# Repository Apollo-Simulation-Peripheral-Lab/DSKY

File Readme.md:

# DSKY Replica
> This project is still a work-in-progress 

This projects aims to create an affordable and easy to manufacture, yet as realistic as possible replica of the DSKY used in the Apollo program to interface with the Apollo Guidance Computer (AGC).

## Quick start

**Do you want a DSKY but can't build one? Buy one [here](https://shop.ortizma.com)**

**Need Help? Join our Discord [here](https://discord.gg/CHZaYj5UNu)**

**Do you just want to have a DSKY display in your web browser?**
  - Make sure you have NodeJS > 18
  - Run start.bat and answer the prompts

**Do you want to build the whole DSKY replica?**
  - Print the .3mf/.stl meshes found in the '3D Models' folder.
    - The recommended display is the **960x544 AMOLED MIPI display**, connected to the Orange Pi via HDMI through an adapter board.
    - A legacy 40-Pin 5" 800x480 LCD variant also exists but is no longer recommended; new builds should use the AMOLED.
  - Order the PCB:
    - The board is designed to be ordered fully assembled from JLCPCB. The fabrication files (gerbers, BOM, pick-and-place positions) are in the ``Boards/Single_board/production`` folder.
  - Calibrate and flash the firmware:
    - Install PlatformIO into VSCode
    - Open this repository's root folder in VSCode — PlatformIO will pick up ``platformio.ini`` at the root
    - Each ATmega328P has a slightly different internal oscillator. You must first determine your chip's optimal OSCCAL value:
      1. Flash the ``bare_calibration`` environment to run the OSCCAL sweep
      2. Use ``firmware/tools/osccal_reader.py`` to read the sweep results and find the best value
      3. Set the ``-DOSC_CAL=0xNN`` flag in ``platformio.ini`` with your value
      4. Flash the ``bare`` environment with your calibrated firmware
  - Set up the Orange Pi:
    - See the [Orange Pi setup guide](Documentation/orangepi-setup.md).
    - Pre-built .img files have been shared around the community, but they are not recommended as they may be out of date.
  - Make sure you have NodeJS > 18
  - Run start.bat on your PC to launch the web display

**Already have a DSKY and want the latest software?**
  - Updates are installed from the DSKY itself: open the menu (press NOUN three times) and go to **SETTINGS → UPDATE**. See [Documentation/updates.md](Documentation/updates.md).

## Repository contents:
* **Documentation**: Useful information to better understand how the different pieces of the puzzle talk to each other. Includes the [Orange Pi setup guide](Documentation/orangepi-setup.md), the [OTA update system](Documentation/updates.md), how to [deploy code to a device over the network](Documentation/deploying-to-a-device.md), and how to [develop on a physical DSKY with hot reload](Documentation/dev-mode.md).
* **2D Models**: SVG files for alarm labels and backlights.
* **3D Models**:
  * **0.4 Nozzle:** All printable meshes (enclosure, display housing, keyboard plate, mounts, etc.) designed for a standard 0.4mm nozzle.
  * **Keys (0.2 Nozzle + AMS).3mf:** Multi-color key models for a 0.2mm nozzle with AMS.
* **Firmware:** PlatformIO project containing the firmware for the bare ATmega328P on the PCB. Includes OSCCAL calibration tooling.
* **Programs:**
  * **next-dsky**: Full-stack Next.js application that serves as the main DSKY UI and backend. Handles serial communication with the PCB, WebSocket connections to AGC simulators, display rendering, and configuration.    * Requirements: NodeJS >18
    * Running: ``npm install`` then ``npm start`` (or use ``start.bat`` from the repo root)
  * **DSKY-Bridge**: Submodule ([nhadrian/DSKY-Bridge](https://github.com/nhadrian/DSKY-Bridge)) — bridge utility for the DSKY.
  * **nassp-cloud**: Node.js service that monitors NASSP (orbiter simulator) telemetry via WebSocket and manages automatic restarts.
  * **click-generator**: Python program that procedurally generates relay clicking audio sequences to emulate the DSKY's relay boxes.
* **Boards**
  * **Single_board**: Unified KiCad PCB project containing the keyboard matrix, alarm lights, serial interface, and backlight driver. The ``production`` folder contains ready-to-order JLCPCB fabrication files.

## License

This project is licensed under [Creative Commons Attribution-NonCommercial-ShareAlike 4.0 International (CC BY-NC-SA 4.0)](LICENSE).

You are free to build one for yourself, modify the design, and share your changes — as long as you **credit the original**, **do not use it commercially**, and **release your derivatives under the same license**. Commercial sale of this device or its derivatives is not permitted without prior written consent from the copyright holder.

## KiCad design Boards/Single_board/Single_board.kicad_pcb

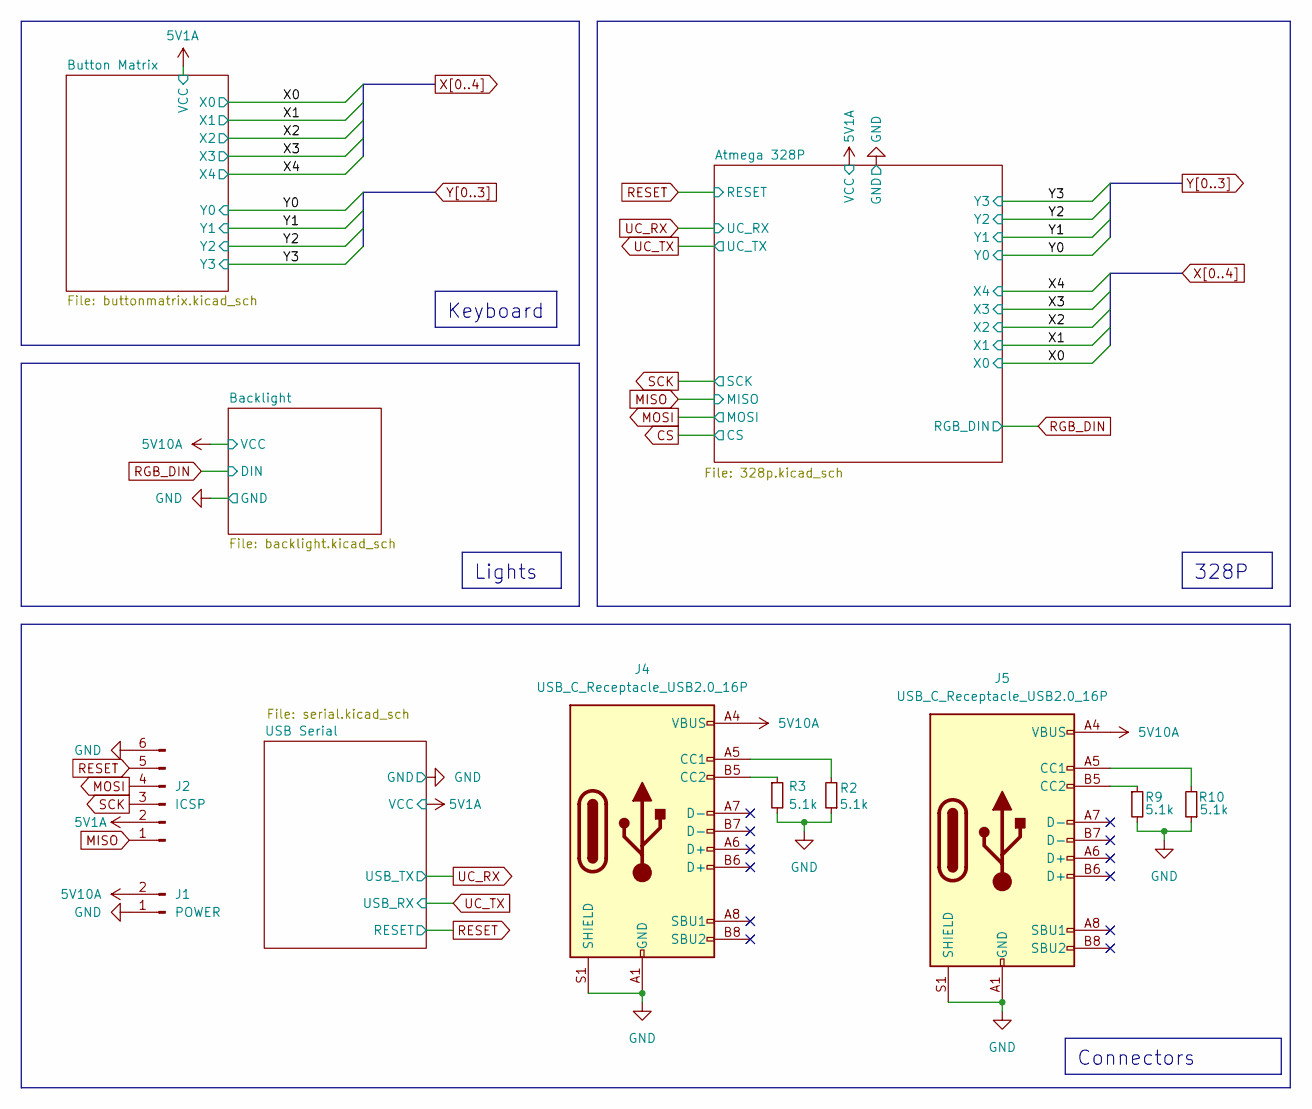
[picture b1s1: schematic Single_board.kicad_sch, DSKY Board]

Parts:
J1: POWER; TerminalBlock_bornier-2_P5.08mm
J2: ICSP; PinHeader_2x03_P2.54mm_Vertical_SMD
J4, J5: USB_C_Receptacle_USB2.0_16P; USB-C-TH_918-468K2029E50001
R2, R3, R9, R10: 5.1k; R_0603_1608Metric

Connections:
5V1A: J2.2; also elsewhere on the board
5V10A: J1.2, J4.A4 (VBUS), J4.A9 (VBUS), J4.B4 (VBUS), J4.B9 (VBUS), J5.A4 (VBUS), J5.A9 (VBUS), J5.B4 (VBUS), J5.B9 (VBUS); also elsewhere on the board
GND: J1.1, J2.6, J4.A1 (GND), J4.A12 (GND), J4.B1 (GND), J4.B12 (GND), J4.S1 (SHIELD), J5.A1 (GND), J5.A12 (GND), J5.B1 (GND), J5.B12 (GND), J5.S1 (SHIELD), R2.1, R3.2, R9.2, R10.1; also elsewhere on the board
MISO: J2.1; also elsewhere on the board
MOSI: J2.4; also elsewhere on the board
unnamed: J4.A5 (CC1), R2.2
unnamed: J4.B5 (CC2), R3.1
unnamed: J5.A5 (CC1), R10.2
unnamed: J5.B5 (CC2), R9.1
RESET: J2.5; also elsewhere on the board
SCK: J2.3; also elsewhere on the board

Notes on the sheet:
Keyboard
328P
Lights
Connectors

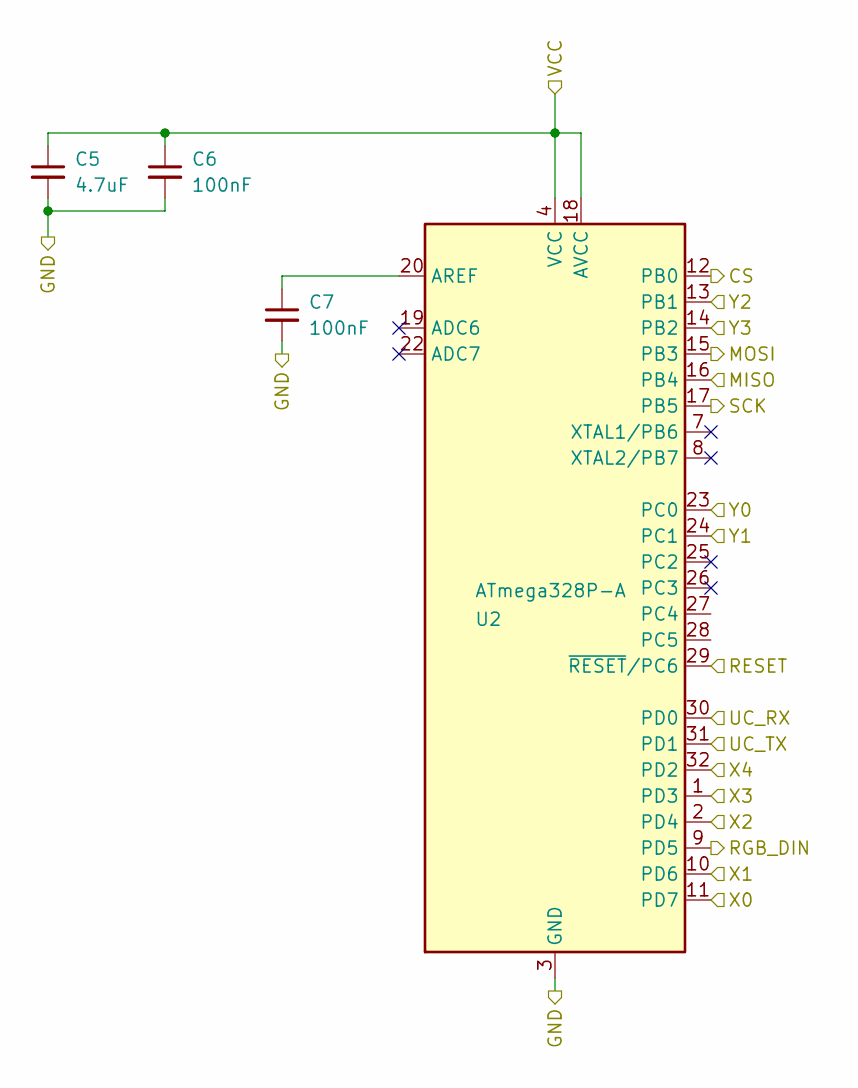
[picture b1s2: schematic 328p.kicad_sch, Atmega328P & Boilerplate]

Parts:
C5: 4.7uF; 0805 4.7uF
C6, C7: 100nF; 0805 100nF
U2: ATmega328P-A; TQFP-32_7x7mm_P0.8mm

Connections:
5V1A: C5.1, C6.1, U2.4 (VCC), U2.6 (VCC), U2.18 (AVCC); also elsewhere on the board
CS: U2.12 (PB0)
GND: C5.2, C6.2, C7.2, U2.3 (GND), U2.5 (GND), U2.21 (GND); also elsewhere on the board
MISO: U2.16 (PB4); also elsewhere on the board
MOSI: U2.15 (PB3); also elsewhere on the board
unnamed: C7.1, U2.20 (AREF)
RESET: U2.29 (~RESET/PC6); also elsewhere on the board
RGB_DIN: U2.9 (PD5); also elsewhere on the board
SCK: U2.17 (PB5); also elsewhere on the board
UC_RX: U2.30 (PD0); also elsewhere on the board
UC_TX: U2.31 (PD1); also elsewhere on the board
X0: U2.11 (PD7); also elsewhere on the board
X1: U2.10 (PD6); also elsewhere on the board
X2: U2.2 (PD4); also elsewhere on the board
X3: U2.1 (PD3); also elsewhere on the board
X4: U2.32 (PD2); also elsewhere on the board
Y0: U2.23 (PC0); also elsewhere on the board
Y1: U2.24 (PC1); also elsewhere on the board
Y2: U2.13 (PB1); also elsewhere on the board
Y3: U2.14 (PB2); also elsewhere on the board

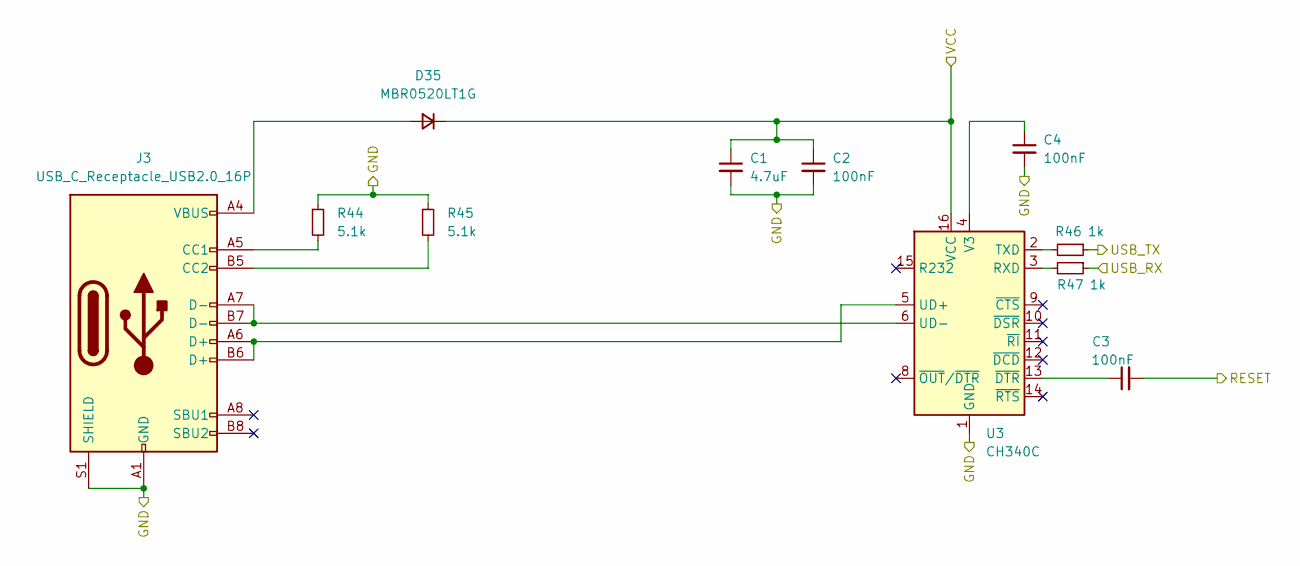
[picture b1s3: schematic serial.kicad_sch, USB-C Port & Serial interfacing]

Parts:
C1: 4.7uF; 0805 4.7uF
C2, C3, C4: 100nF; 0805 100nF
D35: MBR0520LT1G; D_SOD-123
J3: USB_C_Receptacle_USB2.0_16P; USB-C-TH_918-468K2029E50001
R44, R45: 5.1k; R_0603_1608Metric
R46, R47: 1k; R_0603_1608Metric
U3: CH340C; SOIC-16_3.9x9.9mm_P1.27mm

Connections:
5V1A: C1.1, C2.1, D35.1 (K), U3.16 (VCC); also elsewhere on the board
GND: C1.2, C2.2, C4.2, J3.A1 (GND), J3.A12 (GND), J3.B1 (GND), J3.B12 (GND), J3.S1 (SHIELD), R44.1, R45.1, U3.1 (GND); also elsewhere on the board
unnamed: D35.2 (A), J3.A4 (VBUS), J3.A9 (VBUS), J3.B4 (VBUS), J3.B9 (VBUS)
unnamed: J3.A5 (CC1), R44.2
unnamed: J3.B5 (CC2), R45.2
unnamed: R47.2, U3.3 (RXD)
unnamed: R46.2, U3.2 (TXD)
unnamed: J3.A6 (D+), J3.B6 (D+), U3.5 (UD+)
unnamed: J3.A7 (D-), J3.B7 (D-), U3.6 (UD-)
unnamed: C4.1, U3.4 (V3)
unnamed: C3.1, U3.13 (~DTR)
RESET: C3.2; also elsewhere on the board
UC_RX: R46.1; also elsewhere on the board
UC_TX: R47.1; also elsewhere on the board

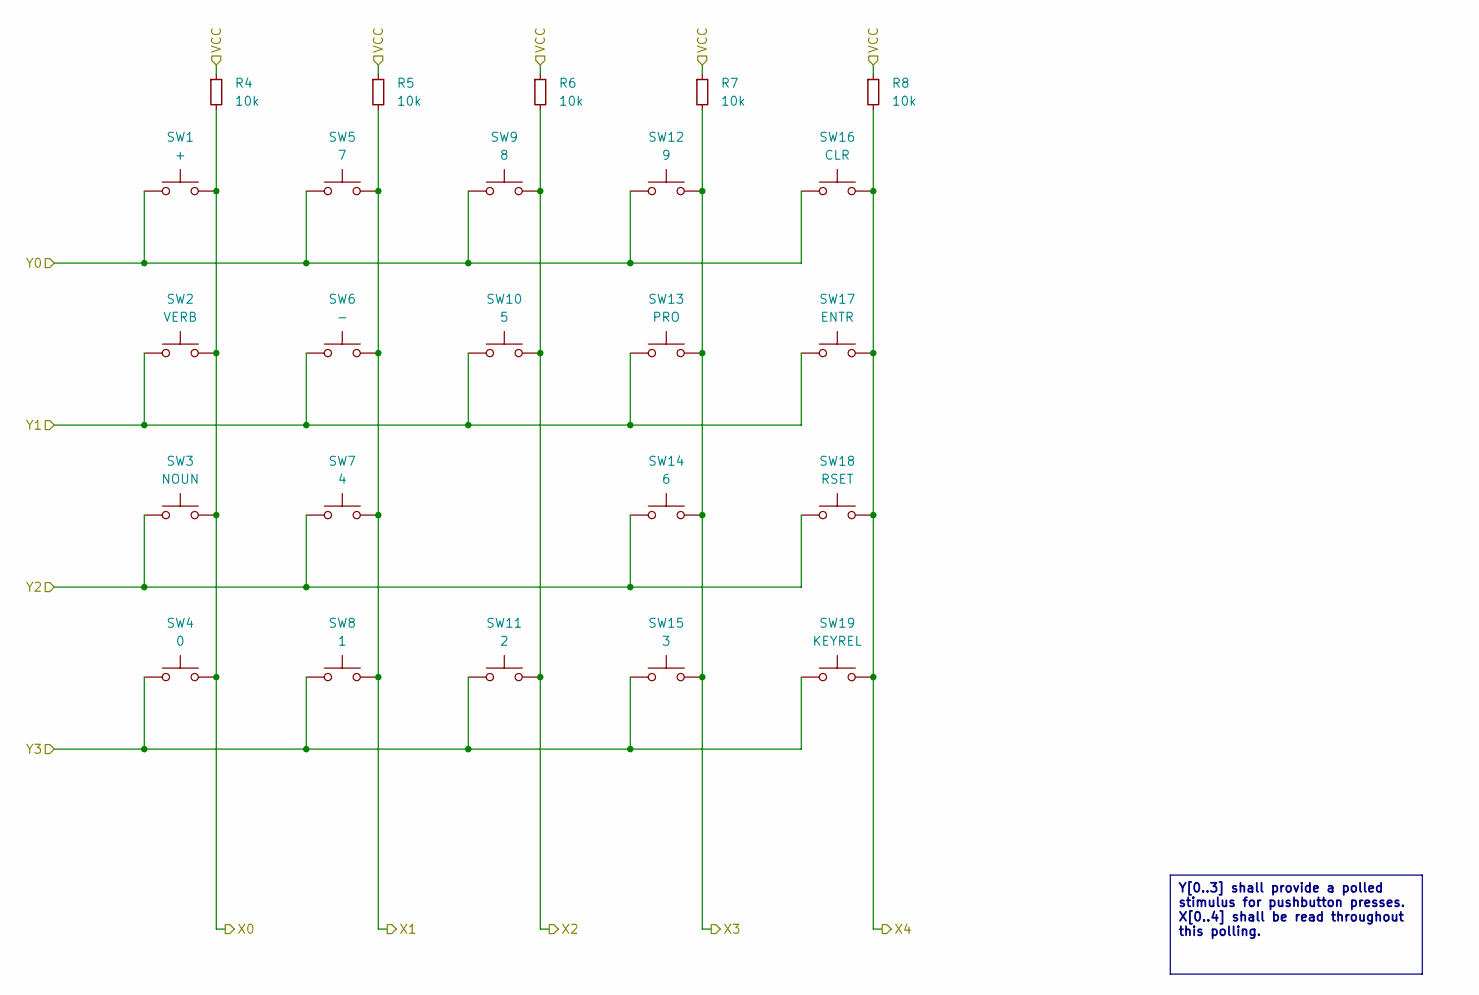
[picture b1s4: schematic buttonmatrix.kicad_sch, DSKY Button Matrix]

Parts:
R4, R5, R6, R7, R8: 10k; R_1206_3216Metric; Part Number CR1206-FX-1002ELF
SW1: +; Kailh_socket_MX
SW2: VERB; Kailh_socket_MX
SW3: NOUN; Kailh_socket_MX
SW4: 0; Kailh_socket_MX
SW5: 7; Kailh_socket_MX
SW6: -; Kailh_socket_MX
SW7: 4; Kailh_socket_MX
SW8: 1; Kailh_socket_MX
SW9: 8; Kailh_socket_MX
SW10: 5; Kailh_socket_MX
SW11: 2; Kailh_socket_MX
SW12: 9; Kailh_socket_MX
SW13: PRO; Kailh_socket_MX
SW14: 6; Kailh_socket_MX
SW15: 3; Kailh_socket_MX
SW16: CLR; Kailh_socket_MX
SW17: ENTR; Kailh_socket_MX
SW18: RSET; Kailh_socket_MX
SW19: KEYREL; Kailh_socket_MX

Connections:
5V1A: R4.1, R5.1, R6.1, R7.1, R8.1; also elsewhere on the board
X0: R4.2, SW1.2, SW2.2, SW3.2, SW4.2; also elsewhere on the board
X1: R5.2, SW5.2, SW6.2, SW7.2, SW8.2; also elsewhere on the board
X2: R6.2, SW9.2, SW10.2, SW11.2; also elsewhere on the board
X3: R7.2, SW12.2, SW13.2, SW14.2, SW15.2; also elsewhere on the board
X4: R8.2, SW16.2, SW17.2, SW18.2, SW19.2; also elsewhere on the board
Y0: SW1.1, SW5.1, SW9.1, SW12.1, SW16.1; also elsewhere on the board
Y1: SW2.1, SW6.1, SW10.1, SW13.1, SW17.1; also elsewhere on the board
Y2: SW3.1, SW7.1, SW14.1, SW18.1; also elsewhere on the board
Y3: SW4.1, SW8.1, SW11.1, SW15.1, SW19.1; also elsewhere on the board

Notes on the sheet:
Y[0..3] shall provide a polled stimulus for pushbutton presses. X[0..4] shall be read throughout this polling.

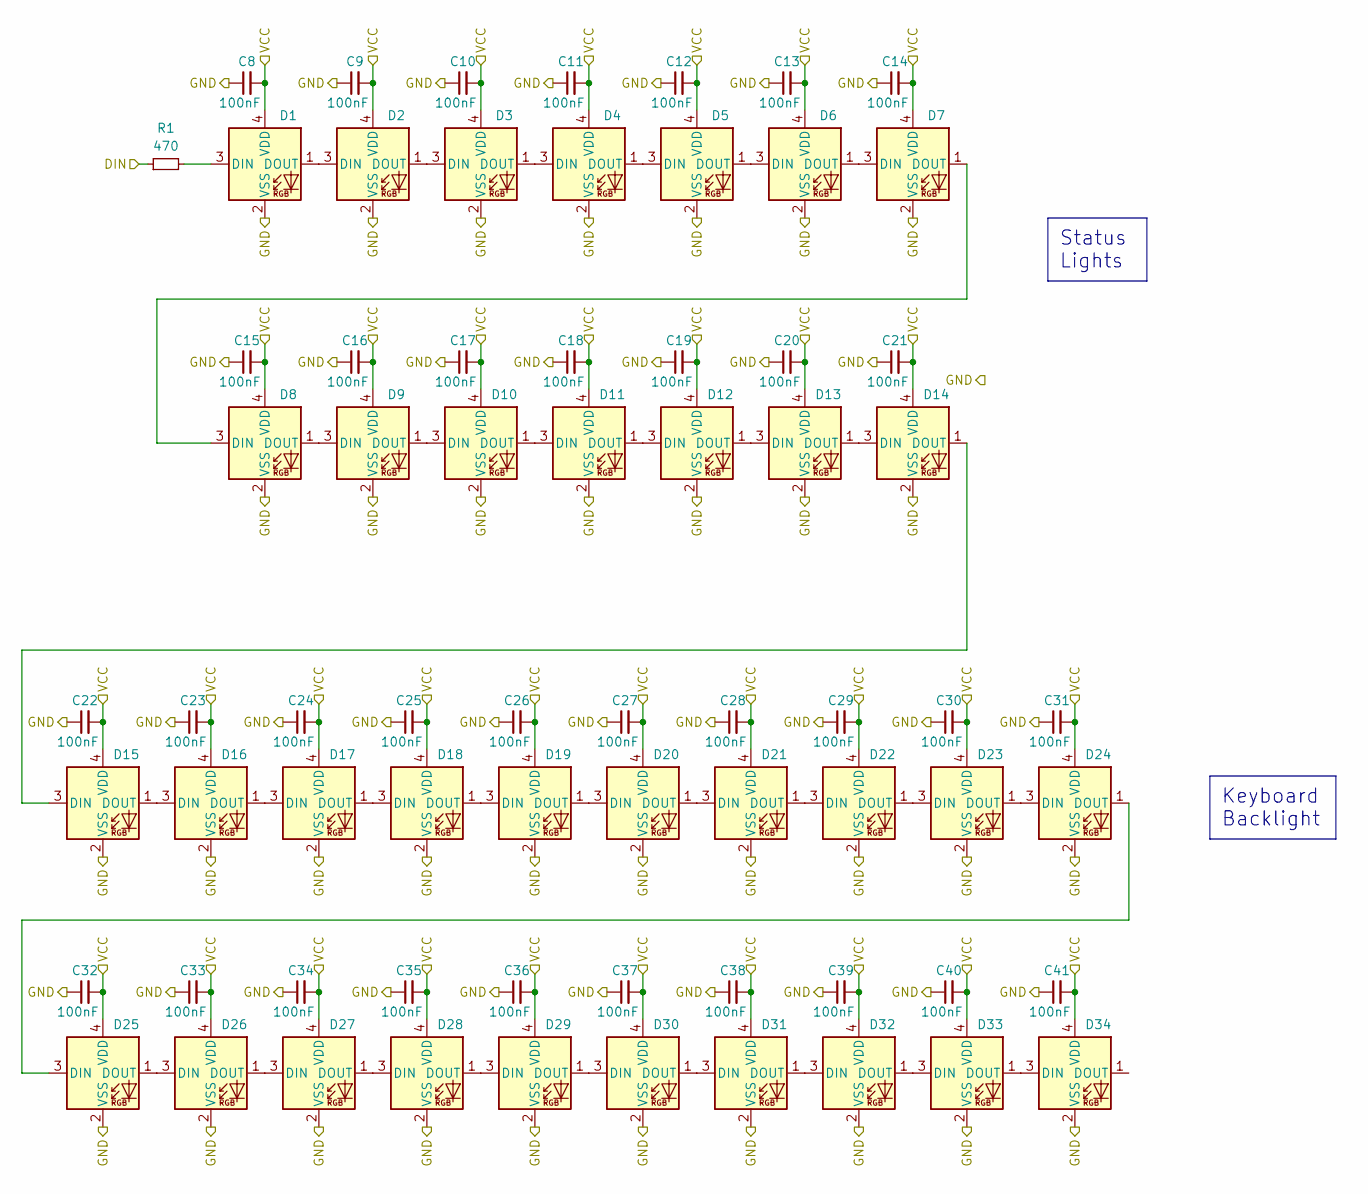
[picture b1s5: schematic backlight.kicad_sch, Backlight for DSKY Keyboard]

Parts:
C8, C9, C10, C11, C12, C13, C14, C15, C16, C17, C18, C19, C20, C21, C22, C23, C24, C25, C26, C27, C28, C29, C30, C31, C32, C33, C34, C35, C36, C37, C38, C39, C40, C41: 100nF; 0805 100nF
D1, D2, D3, D4, D5, D6, D7, D8, D9, D10, D11, D12, D13, D14, D15, D16, D17, D18, D19, D20, D21, D22, D23, D24, D25, D26, D27, D28, D29, D30, D31, D32, D33, D34: SK6812MINI; SK6812-MINI-E
R1: 470; R_0603_1608Metric

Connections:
5V10A: C8.2, C9.2, C10.2, C11.2, C12.2, C13.2, C14.2, C15.2, C16.2, C17.2, C18.2, C19.2, C20.2, C21.2, C22.2, C23.2, C24.2, C25.2, C26.2, C27.2, C28.2, C29.2, C30.2, C31.2, C32.2, C33.2, C34.2, C35.2, C36.2, C37.2, C38.2, C39.2, C40.2, C41.2, D1.4 (VDD), D2.4 (VDD), D3.4 (VDD), D4.4 (VDD), D5.4 (VDD), D6.4 (VDD), D7.4 (VDD), D8.4 (VDD), D9.4 (VDD), D10.4 (VDD), D11.4 (VDD), D12.4 (VDD), D13.4 (VDD), D14.4 (VDD), D15.4 (VDD), D16.4 (VDD), D17.4 (VDD), D18.4 (VDD), D19.4 (VDD), D20.4 (VDD), D21.4 (VDD), D22.4 (VDD), D23.4 (VDD), D24.4 (VDD), D25.4 (VDD), D26.4 (VDD), D27.4 (VDD), D28.4 (VDD), D29.4 (VDD), D30.4 (VDD), D31.4 (VDD), D32.4 (VDD), D33.4 (VDD), D34.4 (VDD); also elsewhere on the board
GND: C8.1, C9.1, C10.1, C11.1, C12.1, C13.1, C14.1, C15.1, C16.1, C17.1, C18.1, C19.1, C20.1, C21.1, C22.1, C23.1, C24.1, C25.1, C26.1, C27.1, C28.1, C29.1, C30.1, C31.1, C32.1, C33.1, C34.1, C35.1, C36.1, C37.1, C38.1, C39.1, C40.1, C41.1, D1.2 (VSS), D2.2 (VSS), D3.2 (VSS), D4.2 (VSS), D5.2 (VSS), D6.2 (VSS), D7.2 (VSS), D8.2 (VSS), D9.2 (VSS), D10.2 (VSS), D11.2 (VSS), D12.2 (VSS), D13.2 (VSS), D14.2 (VSS), D15.2 (VSS), D16.2 (VSS), D17.2 (VSS), D18.2 (VSS), D19.2 (VSS), D20.2 (VSS), D21.2 (VSS), D22.2 (VSS), D23.2 (VSS), D24.2 (VSS), D25.2 (VSS), D26.2 (VSS), D27.2 (VSS), D28.2 (VSS), D29.2 (VSS), D30.2 (VSS), D31.2 (VSS), D32.2 (VSS), D33.2 (VSS), D34.2 (VSS); also elsewhere on the board
unnamed: D1.3 (DIN), R1.2
unnamed: D1.1 (DOUT), D2.3 (DIN)
unnamed: D2.1 (DOUT), D3.3 (DIN)
unnamed: D3.1 (DOUT), D4.3 (DIN)
unnamed: D4.1 (DOUT), D5.3 (DIN)
unnamed: D5.1 (DOUT), D6.3 (DIN)
unnamed: D6.1 (DOUT), D7.3 (DIN)
unnamed: D7.1 (DOUT), D8.3 (DIN)
unnamed: D8.1 (DOUT), D9.3 (DIN)
unnamed: D9.1 (DOUT), D10.3 (DIN)
unnamed: D10.1 (DOUT), D11.3 (DIN)
unnamed: D11.1 (DOUT), D12.3 (DIN)
unnamed: D12.1 (DOUT), D13.3 (DIN)
unnamed: D13.1 (DOUT), D14.3 (DIN)
unnamed: D14.1 (DOUT), D15.3 (DIN)
unnamed: D15.1 (DOUT), D16.3 (DIN)
unnamed: D16.1 (DOUT), D17.3 (DIN)
unnamed: D17.1 (DOUT), D18.3 (DIN)
unnamed: D18.1 (DOUT), D19.3 (DIN)
unnamed: D19.1 (DOUT), D20.3 (DIN)
unnamed: D20.1 (DOUT), D21.3 (DIN)
unnamed: D21.1 (DOUT), D22.3 (DIN)
unnamed: D22.1 (DOUT), D23.3 (DIN)
unnamed: D23.1 (DOUT), D24.3 (DIN)
unnamed: D24.1 (DOUT), D25.3 (DIN)
unnamed: D25.1 (DOUT), D26.3 (DIN)
unnamed: D26.1 (DOUT), D27.3 (DIN)
unnamed: D27.1 (DOUT), D28.3 (DIN)
unnamed: D28.1 (DOUT), D29.3 (DIN)
unnamed: D29.1 (DOUT), D30.3 (DIN)
unnamed: D30.1 (DOUT), D31.3 (DIN)
unnamed: D31.1 (DOUT), D32.3 (DIN)
unnamed: D32.1 (DOUT), D33.3 (DIN)
unnamed: D33.1 (DOUT), D34.3 (DIN)
RGB_DIN: R1.1; also elsewhere on the board

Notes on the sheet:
Status Lights
Keyboard Backlight

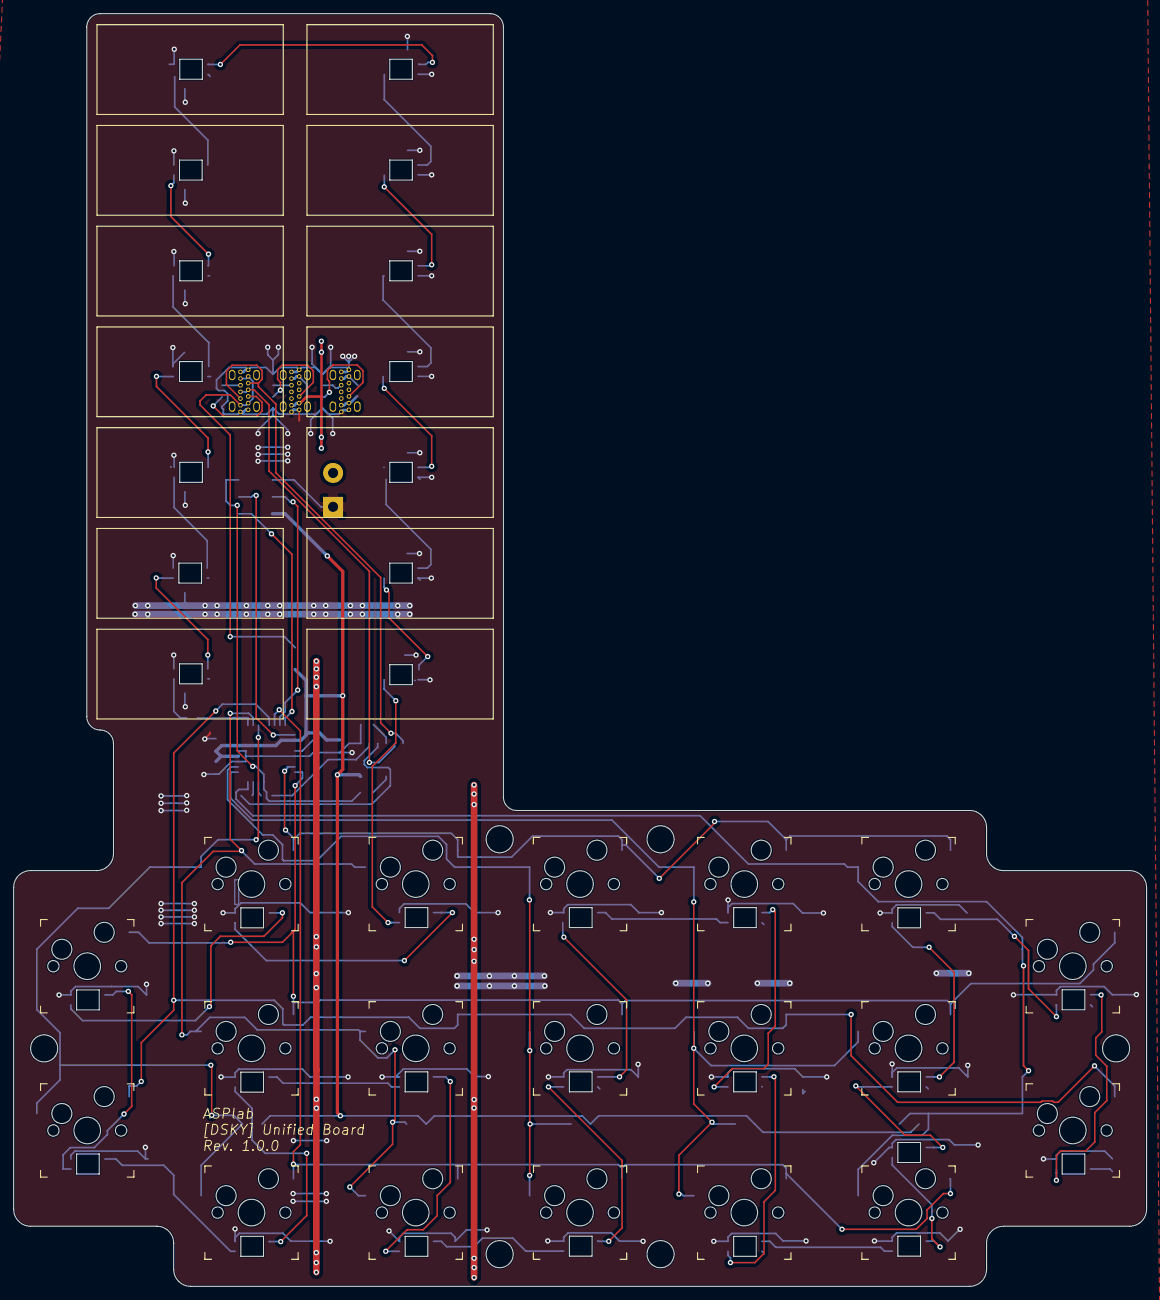
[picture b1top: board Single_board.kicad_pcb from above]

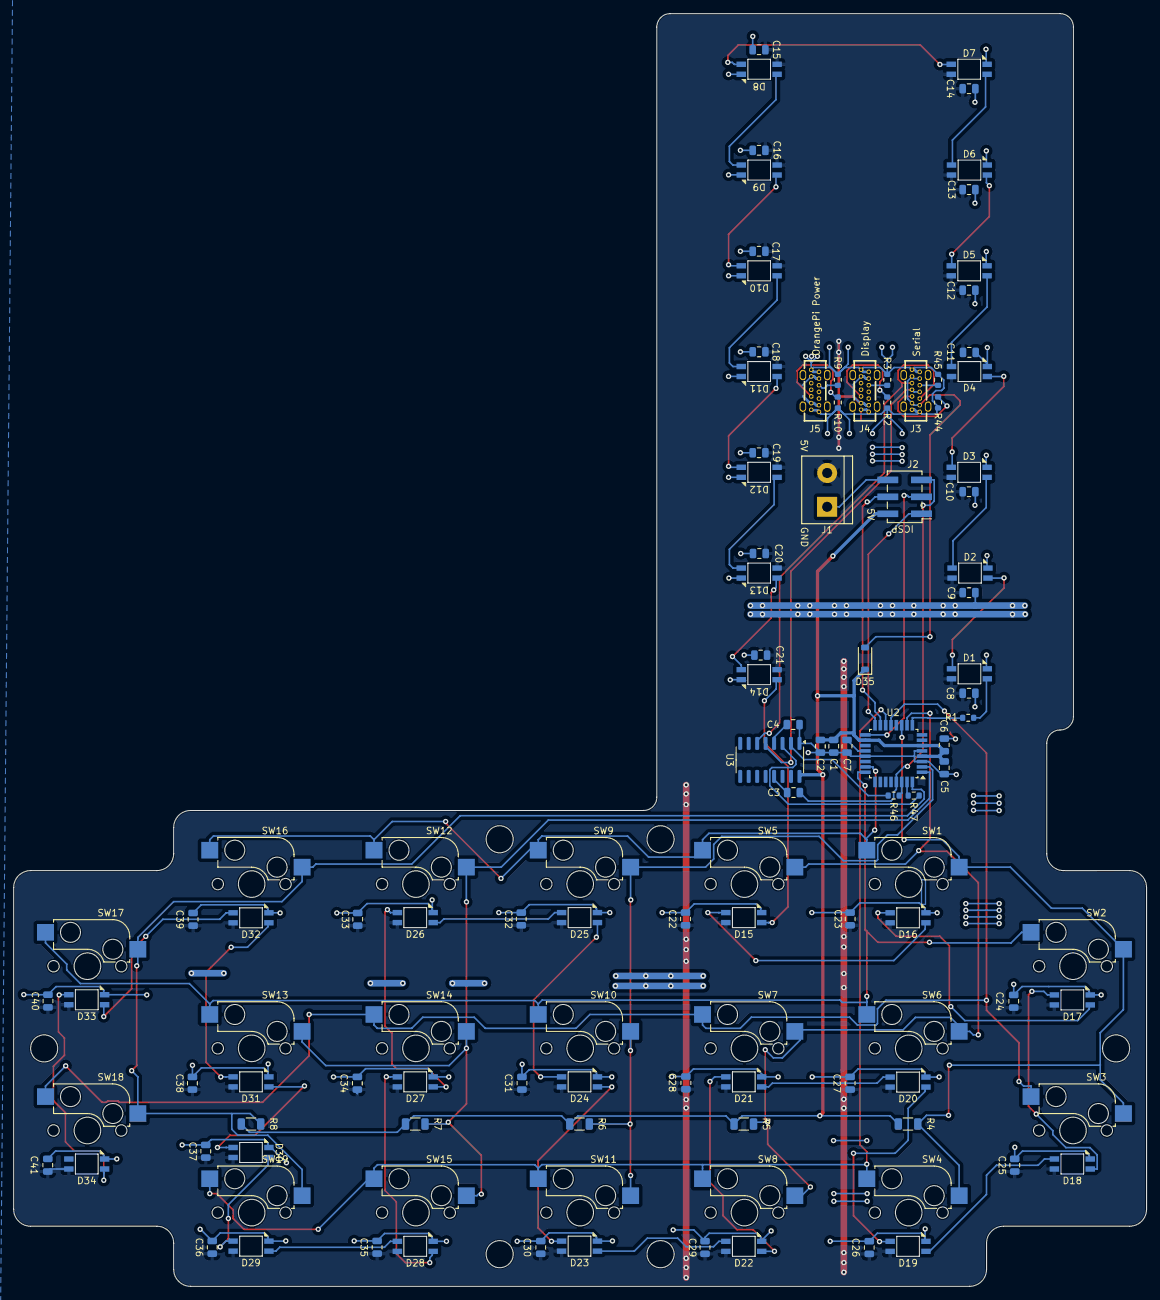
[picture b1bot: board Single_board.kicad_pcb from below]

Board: 2 copper layers, 169.9 x 190.9 mm, 116 parts (97 on the bottom side), 67 nets.

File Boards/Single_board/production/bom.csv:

Designator,Footprint,Quantity,Value,LCSC Part #
"C1, C5",0805 4.7uF,2,4.7uF,C1779
"C10, C11, C12, C13, C14, C15, C16, C17, C18, C19, C2, C20, C21, C22, C23, C24, C25, C26, C27, C28, C29, C3, C30, C31, C32, C33, C34, C35, C36, C37, C38, C39, C4, C40, C41, C6, C7, C8, C9",0805 100nF,39,100nF,C28323
"D1, D10, D11, D12, D13, D14, D15, D16, D17, D18, D19, D2, D20, D21, D22, D23, D24, D25, D26, D27, D28, D29, D3, D30, D31, D32, D33, D34, D4, D5, D6, D7, D8, D9",SK6812-MINI-E,34,SK6812MINI, C5149201
D35,D_SOD-123,1,MBR0520LT1G,
J1,TerminalBlock_bornier-2_P5.08mm,1,POWER,C8465
J2,PinHeader_2x03_P2.54mm_Vertical_SMD,1,ICSP,C192301
"J3, J4, J5",USB-C-TH_918-468K2029E50001,3,USB_C_Receptacle_USB2.0_16P,
R1,0603,1,470,C23179
"R10, R2, R3, R44, R45, R9",0603,6,5.1k,
"R4, R5, R6, R7, R8",1206,5,10k,C17902
"R46, R47",0603,2,1k,C21190
SW1,Kailh_socket_MX,1,+,C2803348
SW10,Kailh_socket_MX,1,5,C2803348
SW11,Kailh_socket_MX,1,2,C2803348
SW12,Kailh_socket_MX,1,9,C2803348
SW13,Kailh_socket_MX,1,PRO,C2803348
SW14,Kailh_socket_MX,1,6,C2803348
SW15,Kailh_socket_MX,1,3,C2803348
SW16,Kailh_socket_MX,1,CLR,C2803348
SW17,Kailh_socket_MX,1,ENTR,C2803348
SW18,Kailh_socket_MX,1,RSET,C2803348
SW19,Kailh_socket_MX,1,KEYREL,C2803348
SW2,Kailh_socket_MX,1,VERB,C2803348
SW3,Kailh_socket_MX,1,NOUN,C2803348
SW4,Kailh_socket_MX,1,0,C2803348
SW5,Kailh_socket_MX,1,7,C2803348
SW6,Kailh_socket_MX,1,-,C2803348
SW7,Kailh_socket_MX,1,4,C2803348
SW8,Kailh_socket_MX,1,1,C2803348
SW9,Kailh_socket_MX,1,8,C2803348
U2,TQFP-32_7x7mm_P0.8mm,1,ATmega328P-A,C14877
U3,SOIC-16_3.9x9.9mm_P1.27mm,1,CH340C,C84681

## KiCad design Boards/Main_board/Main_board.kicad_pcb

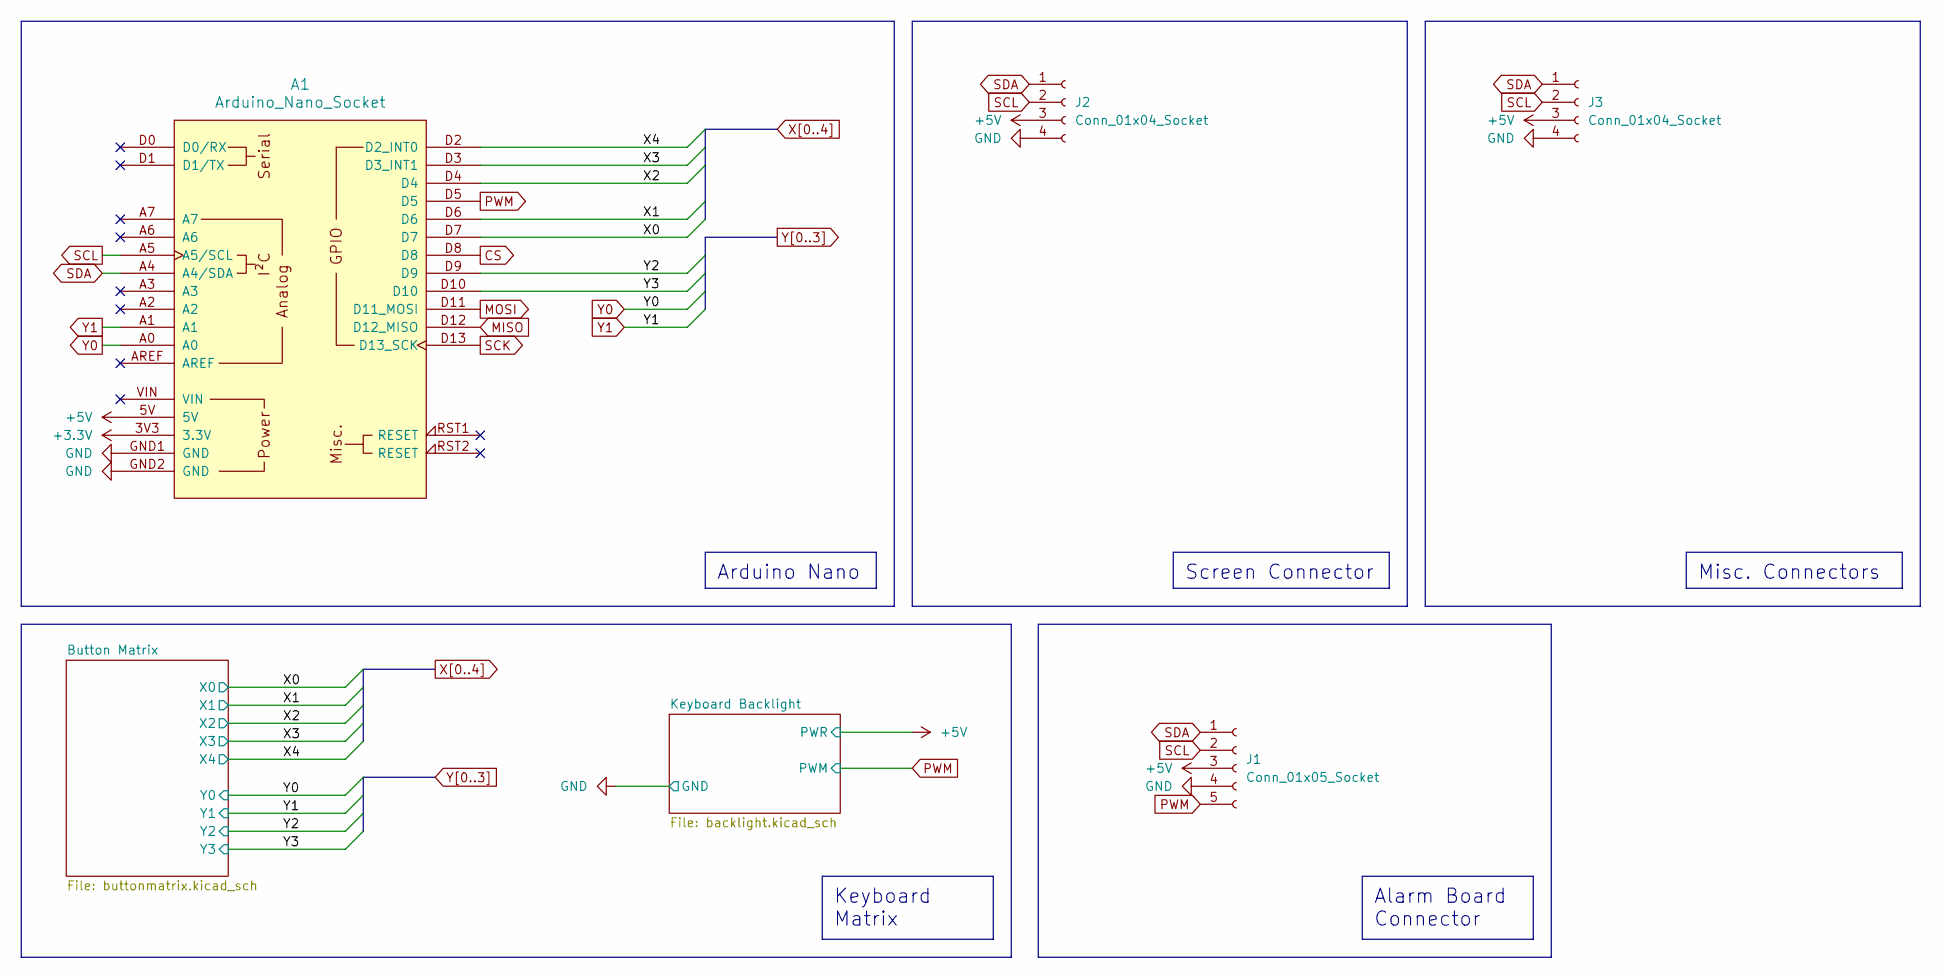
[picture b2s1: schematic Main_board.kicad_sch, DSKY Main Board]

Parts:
A1: Arduino_Nano_Socket
J1: Conn_01x05_Socket; JST_XH_B5B-XH-A_1x05_P2.50mm_Vertical
J2, J3: Conn_01x04_Socket; JST_XH_B4B-XH-A_1x04_P2.50mm_Vertical

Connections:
+3.3V: A1.3V3 (3.3V)
+5V: A1.5V, J1.3, J2.3, J3.3; also elsewhere on the board
CS: A1.D8
GND: A1.GND1 (GND), A1.GND2 (GND), J1.4, J2.4, J3.4; also elsewhere on the board
MISO: A1.D12 (D12_MISO)
MOSI: A1.D11 (D11_MOSI)
PWM: A1.D5, J1.5; also elsewhere on the board
SCK: A1.D13 (D13_SCK)
SCL: A1.A5 (A5/SCL), J1.2, J2.2, J3.2
SDA: A1.A4 (A4/SDA), J1.1, J2.1, J3.1
X0: A1.D7; also elsewhere on the board
X1: A1.D6; also elsewhere on the board
X2: A1.D4; also elsewhere on the board
X3: A1.D3 (D3_INT1); also elsewhere on the board
X4: A1.D2 (D2_INT0); also elsewhere on the board
Y0: A1.A0; also elsewhere on the board
Y1: A1.A1; also elsewhere on the board
Y2: A1.D9; also elsewhere on the board
Y3: A1.D10; also elsewhere on the board

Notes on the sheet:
Screen Connector
Keyboard Matrix
Arduino Nano
Alarm Board Connector
Misc. Connectors

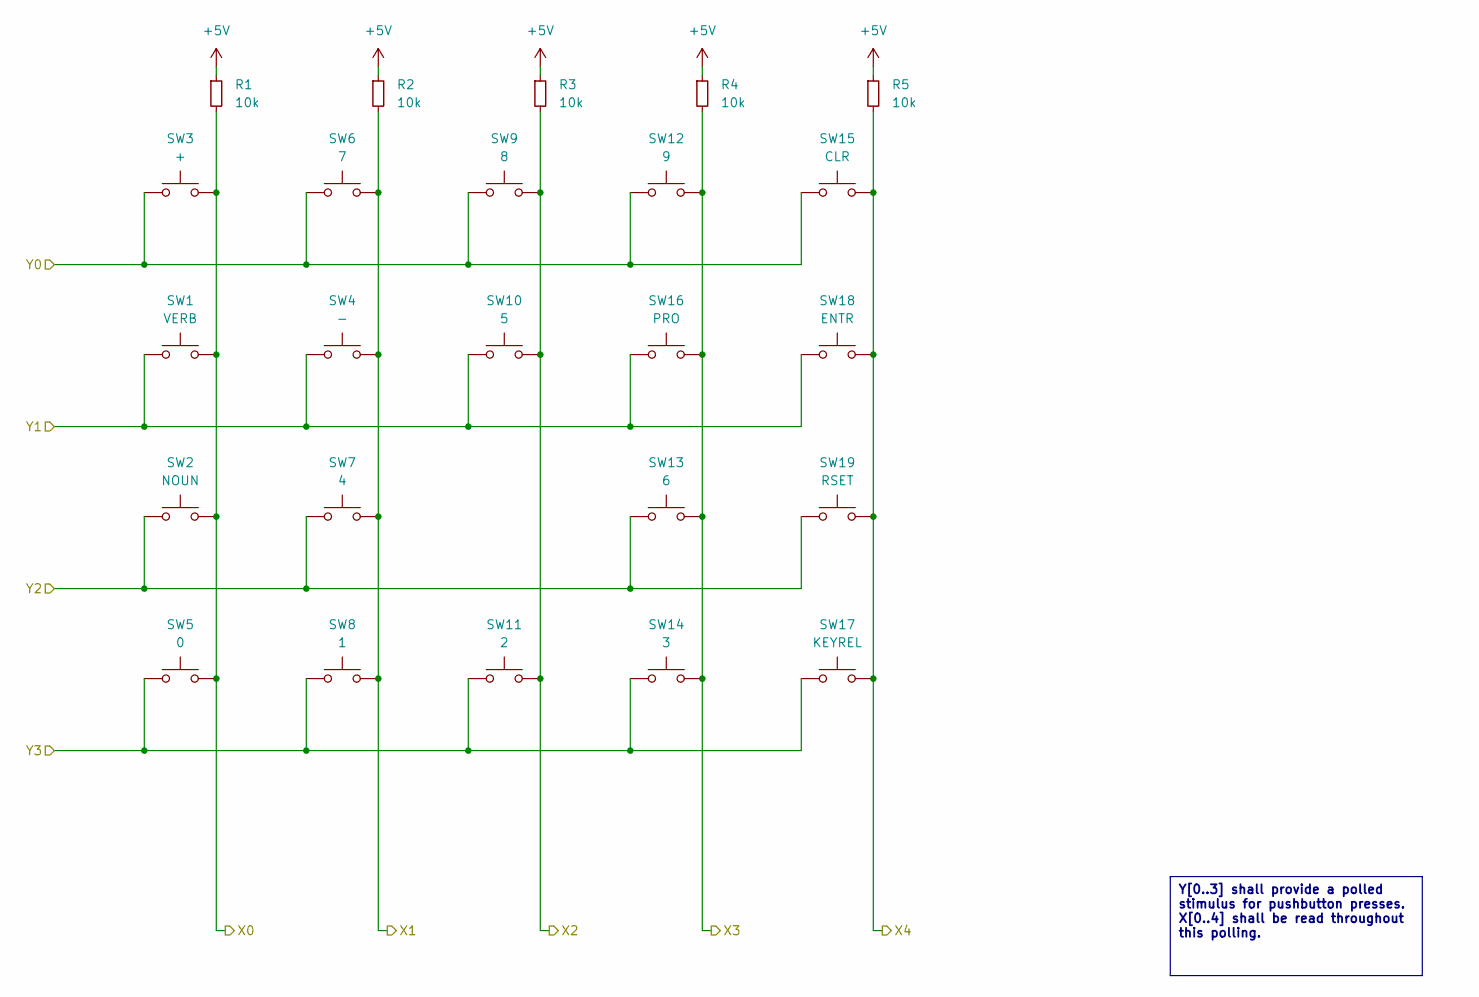
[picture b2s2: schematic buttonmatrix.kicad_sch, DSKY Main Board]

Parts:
R1, R2, R3, R4, R5: 10k; R_1206_3216Metric; Part Number CR1206-FX-1002ELF
SW1: VERB; SW_Cherry_MX_1.00u_Plate
SW2: NOUN; SW_Cherry_MX_1.00u_Plate
SW3: +; SW_Cherry_MX_1.00u_Plate
SW4: -; SW_Cherry_MX_1.00u_Plate
SW5: 0; SW_Cherry_MX_1.00u_Plate
SW6: 7; SW_Cherry_MX_1.00u_Plate
SW7: 4; SW_Cherry_MX_1.00u_Plate
SW8: 1; SW_Cherry_MX_1.00u_Plate
SW9: 8; SW_Cherry_MX_1.00u_Plate
SW10: 5; SW_Cherry_MX_1.00u_Plate
SW11: 2; SW_Cherry_MX_1.00u_Plate
SW12: 9; SW_Cherry_MX_1.00u_Plate
SW13: 6; SW_Cherry_MX_1.00u_Plate
SW14: 3; SW_Cherry_MX_1.00u_Plate
SW15: CLR; SW_Cherry_MX_1.00u_Plate
SW16: PRO; SW_Cherry_MX_1.00u_Plate
SW17: KEYREL; SW_Cherry_MX_1.00u_Plate
SW18: ENTR; SW_Cherry_MX_1.00u_Plate
SW19: RSET; SW_Cherry_MX_1.00u_Plate

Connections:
+5V: R1.1, R2.1, R3.1, R4.1, R5.1; also elsewhere on the board
X0: R1.2, SW1.2, SW2.2, SW3.2, SW5.2; also elsewhere on the board
X1: R2.2, SW4.2, SW6.2, SW7.2, SW8.2; also elsewhere on the board
X2: R3.2, SW9.2, SW10.2, SW11.2; also elsewhere on the board
X3: R4.2, SW12.2, SW13.2, SW14.2, SW16.2; also elsewhere on the board
X4: R5.2, SW15.2, SW17.2, SW18.2, SW19.2; also elsewhere on the board
Y0: SW3.1, SW6.1, SW9.1, SW12.1, SW15.1; also elsewhere on the board
Y1: SW1.1, SW4.1, SW10.1, SW16.1, SW18.1; also elsewhere on the board
Y2: SW2.1, SW7.1, SW13.1, SW19.1; also elsewhere on the board
Y3: SW5.1, SW8.1, SW11.1, SW14.1, SW17.1; also elsewhere on the board

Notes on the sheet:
Y[0..3] shall provide a polled stimulus for pushbutton presses. X[0..4] shall be read throughout this polling.
